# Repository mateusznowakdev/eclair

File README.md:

# EclairM0

[Project description](https://mateusznowak.dev/eclair) and [build instructions](https://mateusznowak.dev/eclair/build) can be found on my website.

Hardware files can be previewed in these third-party web applications:

- KiCad files (board) -- https://kicanvas.org
- OpenSCAD files (enclosure) -- https://openscad.cloud/openscad/

License terms for software and hardware are present in the [LICENSE.md](./LICENSE.md) file.

Jump to:

- [building firmware from source](#building-firmware-from-source)
- [updating font data](#updating-font-data)
- [3D-printing the enclosure](#3d-printing-the-enclosure)
- [engraving button labels](#engraving-button-labels)
- [changelog](#changelog)

---

## Building firmware from source

Install the TinyGo SDK. Copy EclairM0 board definition files as follows:

| File from this repo                | Target SDK directory |
|------------------------------------|----------------------|
| firmware/_board/board_eclair-m0.go | src/machine          |
| firmware/_board/eclair-m0.json     | targets              |
| firmware/_board/eclair-m0.ld       | targets              |

Now you should be able to build and upload new firmware, like this:

```bash
cd firmware
tinygo flash -target eclair-m0 -size short
```

## Updating sprite data

Raw pixel data is stored in PGM (portable graymap) files, editable with GIMP. Spritesheet images must be 8px or 16px tall. The background is white, the foreground is black, and the mask information is gray/black (used when rendering sprites on top of each other).

Source files can be converted into a working Go code, using the `tools/make_spritesheet_data.py` script, which should work with any modern version of Python:

```bash
cd tools
python3 make_spritesheet_data.py path/to/file.pgm path/to/file.txt
```

## 3D-printing the enclosure

Creality Ender-3 V3 KE is my 3D printer. I'm using OrcaSlicer 2.2.0, and at this point I'm too scared to update :)

These are the printing settings recommended by me:

- Global filament settings (PLA) &rarr; 215&deg;C nozzle, 60&deg;C bed
- "0.12mm Fine" base preset
- Quality &rarr; Seam position: BACK
- Quality &rarr; Scarf joint seam: CONTOUR
- Quality &rarr; Elephant foot compensation: 0.15mm (depends on the printer calibration, default is 0.05mm)
- Quality &rarr; Precise wall: ON
- Quality &rarr; Walls printing order: INNER/OUTER
- Quality &rarr; Detect overhang walls: OFF
- Strength &rarr; Bottom surface pattern: ARCHIMEDEAN or HILBERT for best appearance
- Speed &rarr; First layer: 20mm/s (default is 50mm/s and it's too fast)
- Speed &rarr; Top surface: 100mm/s (default is 250mm/s)

Supports should not be necessary for the bridge under the slide switch cutout.

Any bright filament (yellow, white) would hide most of the inaccuracies, and it will also make the engraved letters more visible.

## Engraving button labels

Gerber files generated by KiCad can be converted to a G-code compatible with many desktop CNCs. If you happen to use `pcb2gcode`, the example config is available in the repo.

It's difficult to get it right the first try, because:

- the router table is never perfectly flat
- the enclosure is thin and can bend a little
- auto-generated toolpaths may result in thicker cuts for some letters
- some PLA types melt too soon

The best idea is to set the spindle so it barely touches the enclosure at the highest point. Start cutting all letters at once, and lower the spindle at 0.1mm increments. If any letter pair looks okay (at about 0.3mm deep), remove it from the job file and repeat.

## Changelog

### Software

Version 1.3:

- Added two more slots for notes, for a total of 5
- Changed the user interface in all apps

Version 1.2:

- Added two more slots for notes

Version 1.1:

- Added Shift key, and the menu for inserting symbols and some keyboard keys
- Changed font to NewStroke
- Changed USB VID/PID and manufacturer/device name
- Changed battery voltage measurement code 
  - **Replace resistors before updating -- see Rev.D changelog below**

Version 1.0:

- Initial version

### Hardware

Rev.D:

- Switched to LIR2025(H) battery
- Changed R51 and R52 resistors, to 22K and 5.1K respectively, to have 1V max output

Rev.C:

- Added ADC/DAC test point, and extra soldering pad for attaching the unmodified Li-Po battery

Rev.B:

- Added Schottky diode to prevent battery from back-powering the USB host
- Added 5V, 3.3V and extra GND test points

Rev.A:

- Initial revision

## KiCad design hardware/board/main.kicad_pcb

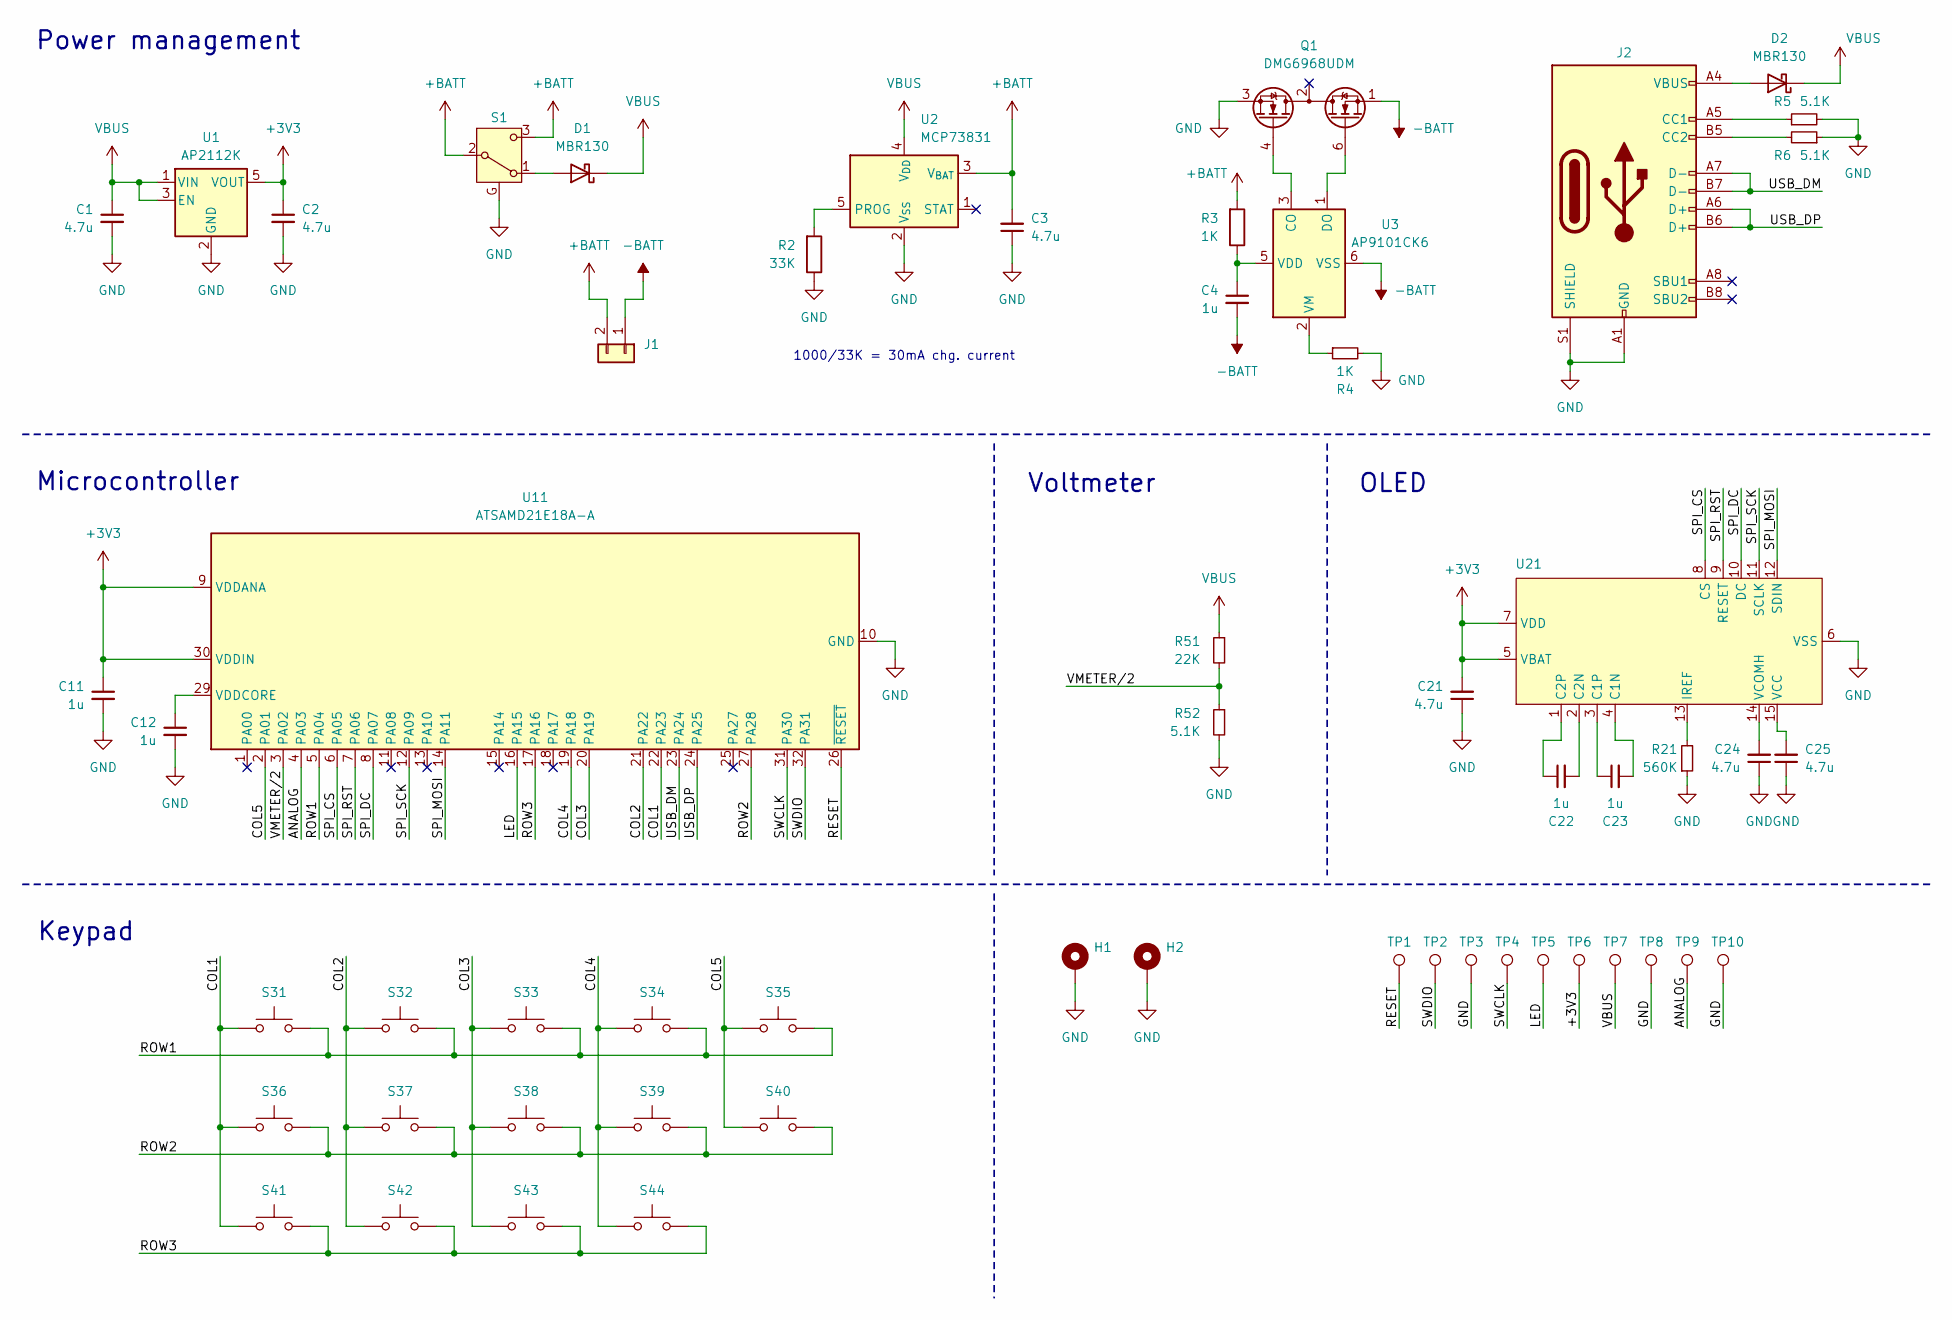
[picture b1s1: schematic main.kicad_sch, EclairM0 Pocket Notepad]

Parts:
C1, C2, C3, C21, C24, C25: 4.7u; C_0805_2012Metric
C4, C11, C12, C22, C23: 1u; C_0805_2012Metric
D1, D2: MBR130; D_1206_3216Metric
H1, H2: MountingHole_2.2mm_M2_Pad_Small
J1: LP301525
J2: USB_C_Receptacle_GCT_USB4105-xx-A_16P_TopMnt_Horizontal
Q1: DMG6968UDM; SOT-23-6
R2: 33K; R_0805_2012Metric
R3, R4: 1K; R_0805_2012Metric
R5, R6, R52: 5.1K; R_0805_2012Metric
R21: 560K; R_0805_2012Metric
R51: 22K; R_0805_2012Metric
S1: SW_SPDT; SW_SPDT_PCM12
S31, S32, S33, S34, S35, S36, S37, S38, S39, S40, S41, S42, S43, S44: SW_SPST_EVQQ2
TP1, TP2, TP3, TP4, TP5, TP6, TP7, TP8, TP9: TestPoint_Pad_D1.0mm
TP10: TestPoint_Pad_2.0x2.5mm
U1: AP2112K; SOT-23-5
U2: MCP73831; SOT-23-5
U3: AP9101CK6; SOT-23-6
U11: ATSAMD21E18A-A; TQFP-32_7x7mm_P0.8mm
U21: REX012832

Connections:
+3V3: C2.1, C11.1, C21.2, TP6.1, U1.5 (VOUT), U11.9 (VDDANA), U11.30 (VDDIN), U21.5 (VBAT), U21.7 (VDD)
+BATT: C3.2, J1.2, R3.2, S1.2 (B), S1.3 (C), U2.3 (V_{BAT})
-BATT: C4.2, J1.1, Q1.1 (D1), U3.6 (VSS)
/ANALOG: TP9.1, U11.4 (PA03)
/COL1: S31.1, S36.1, S41.1, U11.22 (PA23)
/COL2: S32.1, S37.1, S42.1, U11.21 (PA22)
/COL3: S33.1, S38.1, S43.1, U11.20 (PA19)
/COL4: S34.1, S39.1, S44.1, U11.19 (PA18)
/COL5: S35.1, S40.1, U11.2 (PA01)
/LED: TP5.1, U11.16 (PA15)
/RESET: TP1.1, U11.26 (~RESET)
/ROW1: S31.2, S32.2, S33.2, S34.2, S35.2, U11.5 (PA04)
/ROW2: S36.2, S37.2, S38.2, S39.2, S40.2, U11.27 (PA28)
/ROW3: S41.2, S42.2, S43.2, S44.2, U11.17 (PA16)
/SPI_CS: U11.6 (PA05), U21.8 (CS)
/SPI_DC: U11.8 (PA07), U21.10 (DC)
/SPI_MOSI: U11.14 (PA11), U21.12 (SDIN)
/SPI_RST: U11.7 (PA06), U21.9 (RESET)
/SPI_SCK: U11.12 (PA09), U21.11 (SCLK)
/SWCLK: TP4.1, U11.31 (PA30)
/SWDIO: TP2.1, U11.32 (PA31)
/USB_DM: J2.A7 (D-), J2.B7 (D-), U11.23 (PA24)
/USB_DP: J2.A6 (D+), J2.B6 (D+), U11.24 (PA25)
/VMETER/2: R51.2, R52.1, U11.3 (PA02)
GND: C1.2, C2.2, C3.1, C11.2, C12.2, C21.1, C24.1, C25.1, H1.1, H2.1, J2.A1 (GND), J2.A12 (GND), J2.B1 (GND), J2.B12 (GND), J2.S1 (SHIELD), Q1.3 (S2), R2.1, R4.2, R5.2, R6.1, R21.1, R52.2, S1.G, TP3.1, TP8.1, TP10.1, U1.2 (GND), U2.2 (V_{SS}), U11.10 (GND), U11.28 (GND), U21.6 (VSS)
unnamed: D1.2 (A), S1.1 (A)
unnamed: D2.2 (A), J2.A4 (VBUS), J2.A9 (VBUS), J2.B4 (VBUS), J2.B9 (VBUS)
unnamed: J2.A5 (CC1), R5.1
unnamed: J2.B5 (CC2), R6.2
unnamed: Q1.6 (G1), U3.1 (DO)
unnamed: Q1.4 (G2), U3.3 (CO)
unnamed: R2.2, U2.5 (PROG)
unnamed: C4.1, R3.1, U3.5 (VDD)
unnamed: R4.1, U3.2 (VM)
unnamed: C12.1, U11.29 (VDDCORE)
unnamed: C23.2, U21.4 (C1N)
unnamed: C23.1, U21.3 (C1P)
unnamed: C22.2, U21.2 (C2N)
unnamed: C22.1, U21.1 (C2P)
unnamed: R21.2, U21.13 (IREF)
unnamed: C25.2, U21.15 (VCC)
unnamed: C24.2, U21.14 (VCOMH)
VBUS: C1.1, D1.1 (K), D2.1 (K), R51.1, TP7.1, U1.1 (VIN), U1.3 (EN), U2.4 (V_{DD})

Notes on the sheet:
Microcontroller
Voltmeter
OLED
1000/33K = 30mA chg. current
Keypad
Power management

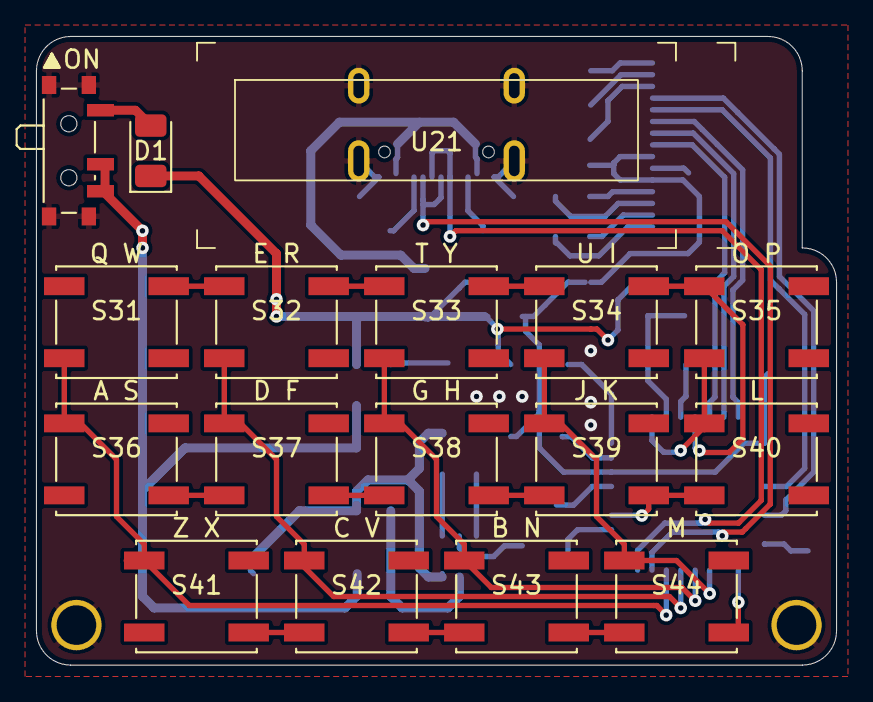
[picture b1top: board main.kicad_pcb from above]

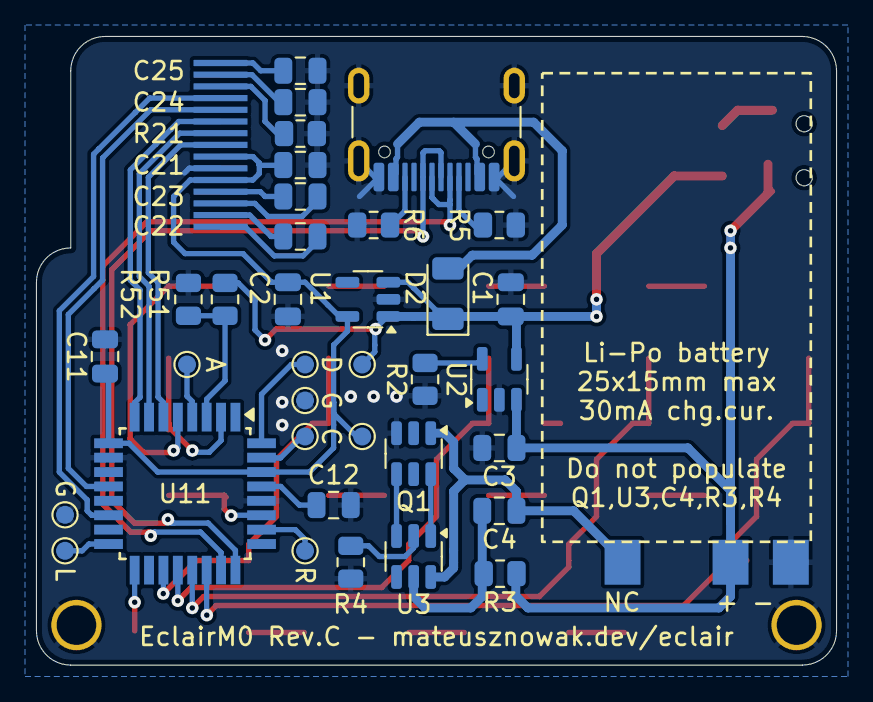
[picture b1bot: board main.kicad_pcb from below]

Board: 4 copper layers, 44.5 x 34.9 mm, 56 parts (37 on the bottom side), 43 nets.

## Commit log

2025-04-05 Create new repo
2025-04-05 Prepare files for public release
2025-04-08 Update board files
    Added extra pad, so the battery can be connected without removing the protection circuit
2025-04-19 Update enclosure files
    Fix misaligned display hole, slightly change lid snaps' positions
2025-04-23 Update battery footprint
    Remove solder paste from battery pads
2025-04-23 Update project name to improve discoverability
2025-06-04 Update indicator icons, generate these from PBM file
2025-06-04 Add the character picker app
2025-06-04 Add changelog to the README
2025-06-04 Create main enclosure from scratch
    Move origin to the center, update dimensions to match reality even more, simplify math, add comments when necessary, add supports to protect the display
2025-06-04 Change how current launcher entry is highlighted
2025-06-04 Update font data
    Use modified version of NewStroke which is KiCad font used to engrave enclosure's labels. Add missing glyphs to get full ASCII support. Generate glyph data from PBM image, remove old HTML editor.
2025-06-04 Add custom board definition to CI pipeline
2025-06-04 Clean HAL function names
    New smaller modules had duplicated information in function names, for example watchdog.FeedWatchdog(). This is now simplified to just watchdog.Feed()
2025-06-04 Display popup menu for inserting new characters into a note
2025-06-04 Add extra actions in popup menu
    Arrow keys, Enter, Backspace, Tab and Escape should be enough to make EclairM0 a keyboard / macropad for basic needs
2025-06-04 Replace basic supports with snap joints
2025-06-04 Add 1px extra horizontal spacing between glyphs
2025-06-04 Change battery measurement circuit
    Use 22K / 5.1K voltage divider and fixed 1V reference. This should work correctly even if system voltage goes below 3.3V.
2025-06-04 Panic instead of locking CPU on failed read/write, it gives the same result
2025-06-04 Replace Li-Po battery with rechargeable coin battery
    Charging circuit has been moved closer to the USB. The slide switch is now mounted on the bottom layer. Battery protection circuit is removed due to lack of space. Updated for KiCad 9.0.2, optimized 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
2025-06-04 Add brief instructions on how to set up TinyGo SDK
2025-06-04 Make it possible to leave popup menu without selecting a symbol
2025-06-04 Update slide switch file
2025-06-04 Change shape of lowercase letter S
2025-06-04 Update enclosure lid file
2025-06-04 Update drivers to version that includes the SSD1306 SPI fix
2025-06-04 Add custom TinyGo board definition
    Do not use Trinket M0 as a base anymore. This allows me to set custom USB VID/PID and default pins.
2025-06-04 Add custom code for mapping ASCII characters to key presses
    This is compatible with US English keyboard layout, which happens to be used in Poland where I live. Compared to TinyGo default implementation, none of these characters will be handled as if they con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
2025-06-04 Create single HAL directory
    Move existing "large" modules there (display, keypad), split peripherals module into smaller ones
2025-06-04 Add Shift key for entering uppercase characters
2025-06-11 Fix invalid padding for some icons
2025-06-11 Use built-in watchdog implementation
2025-06-12 Clean up event handlers and app-level functions
    Instead of passing disp, keys and bat references in functions and event handlers, have these at the package level
2025-06-17 Update TinyGo and drivers
2025-06-18 Use X and Y coordinates when drawing things
2025-06-18 Implement horizontal alignment for text and sprites
2025-06-18 Use littlefs for storage
2025-06-18 Implement lightweight filesystem - stub functions
2025-06-19 Implement lightweight filesystem
2025-06-22 Use custom filesystem to store note data
    On SAMD21, it allows for creating up to 15 files, 256 bytes each
2025-06-22 Create app for formatting the internal storage
    The shortcut ZX+CV has been removed because it's no longer necessary.
2025-06-22 Create three note slots, by default open the first one
2025-06-22 Explicitly ignore some error return values
2025-06-22 Handle 8px and 16px tall sprites
2025-06-30 Make display cutout slightly larger near the top
2025-06-30 Export STL files and PCB schematic
2025-06-30 Add missing changelog entry
2025-07-05 Update spritesheet generation tool
    All sprites are now 8px tall. If spritesheet is 16px tall, then it will be split in half. Source files are now PGM (grayscale), with gray color used for masking.
2025-07-05 Use the new sprite engine
    Font data is stored as 8px sprites that will be combined into 16px glyphs when rendering. Other functions are updated accordingly.
2025-07-05 Move stuff related to multiline rendering into a separate file
2025-07-05 Use icons in the launcher, mapped to first two rows of buttons
2025-07-05 Hide bootloader launcher entry, activate with ZX + BN
2025-07-05 Fix missing cursor when text is empty
2025-07-05 Restore "delete single line" function
2025-07-06 Display character map items on a grid
2025-07-06 Update UI for mouse flashlight apps
2025-07-06 Add countdown and update UI for erase app
2025-07-06 Handle drawing sprites out of bounds
2025-07-06 Rename spritesheet data generator script
2025-07-06 Add screenshot feature and a script to process captured screenshot data
2025-07-06 Add separator between navigation buttons and choice buttons in charmap app
2025-07-29 Update changelog
